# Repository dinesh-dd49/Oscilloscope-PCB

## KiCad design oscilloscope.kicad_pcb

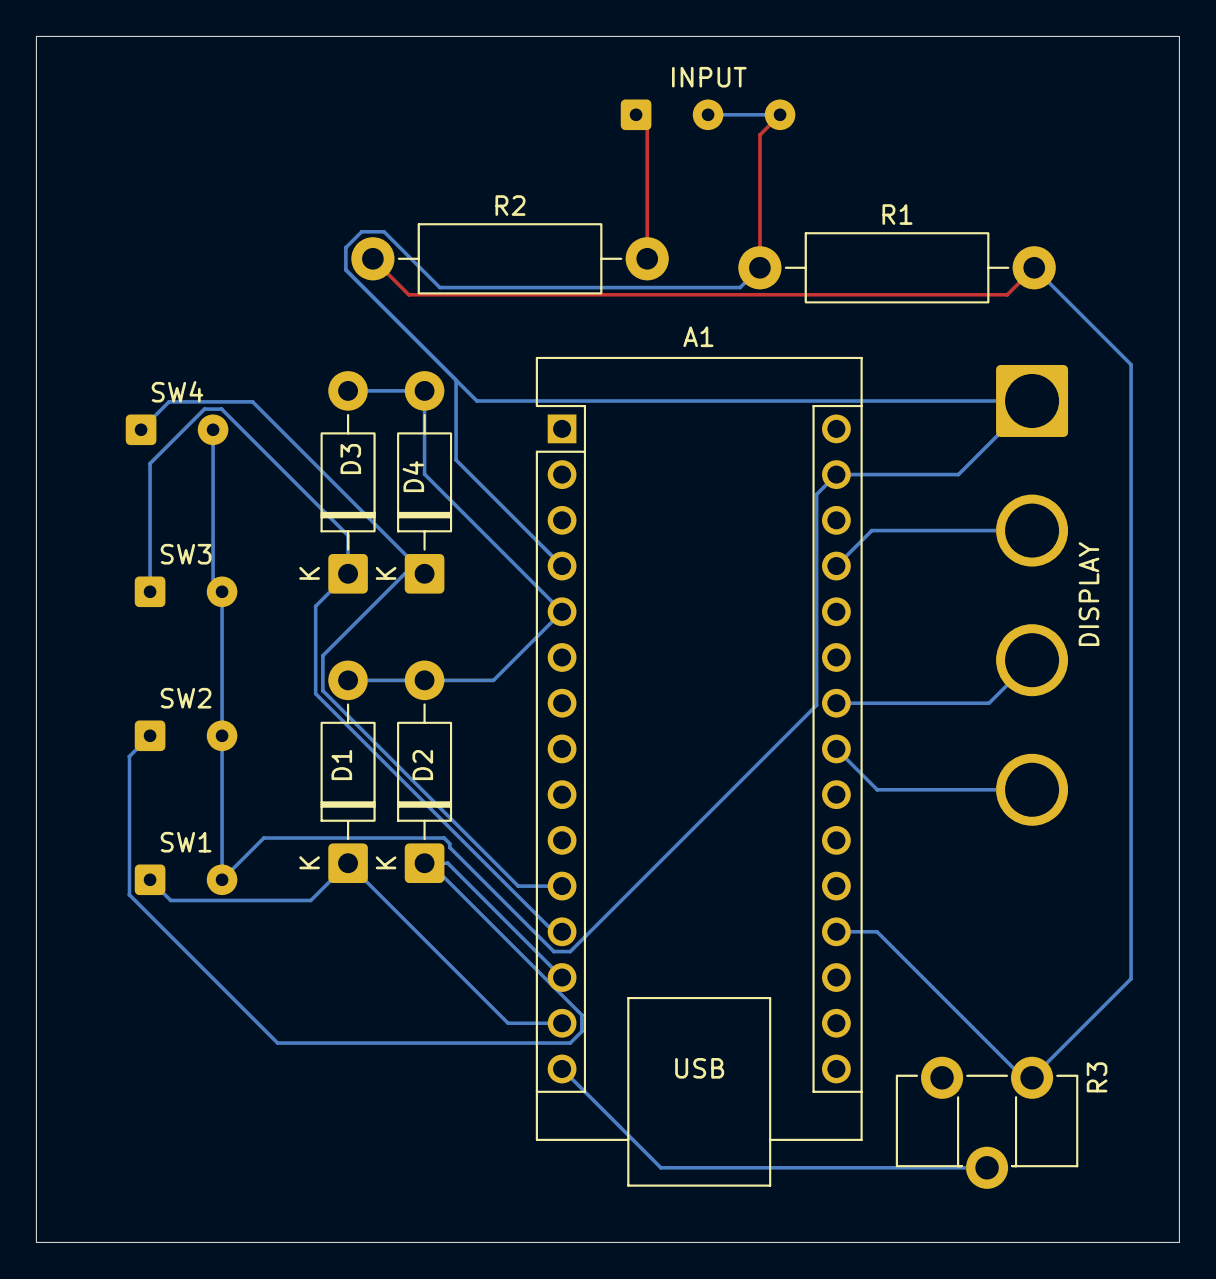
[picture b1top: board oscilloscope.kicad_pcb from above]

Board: 2 copper layers, 63.5 x 67.0 mm, 14 parts (0 on the bottom side), 12 nets.

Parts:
A1: Arduino_Nano_v3.x; Arduino_Nano
D1, D2, D3, D4: 1N4007; D_DO-41_SOD81_P10.16mm_Horizontal
DISPLAY: ER_OLEDM0.91_1x-I2C; SolderWire-2.5sqmm_1x04_P7.2mm_D2.4mm_OD3.6mm
INPUT: Barrel_Jack_Switch_Pin3Ring; SolderWire-0.15sqmm_1x03_P4mm_D0.5mm_OD1.5mm
R1: 100k; R_Axial_DIN0411_L9.9mm_D3.6mm_P15.24mm_Horizontal
R2: 390K; R_Axial_DIN0411_L9.9mm_D3.6mm_P15.24mm_Horizontal
R3: 10K; Potentiometer_ACP_CA9-H5_Horizontal
SW1, SW2, SW3, SW4: SW_Push; SolderWire-0.15sqmm_1x02_P4mm_D0.5mm_OD1.5mm

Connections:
/K1: A1.14 (D11), D1.1 (K), SW1.1
/K2: A1.13 (D10), D2.1 (K), SW2.1
/K3: A1.12 (D9), D3.1 (K), SW3.1
/K4: A1.11 (D8), D4.1 (K), SW4.1
/di: A1.5 (D2), D1.2 (A), D2.2 (A), D3.2 (A), D4.2 (A)
/dis_vol: A1.27 (+5V), DISPLAY.2 (VCC)
/scl: A1.24 (A5), DISPLAY.3 (SCL)
/sda: A1.23 (A4), DISPLAY.4 (SDA)
/sig: A1.19 (A0), R1.2, R2.1, R3.1
/sig_in: INPUT.1, R2.2
GND: A1.4 (GND), A1.29 (GND), DISPLAY.1 (GND), INPUT.2, INPUT.3, R1.1, SW1.2, SW2.2, SW3.2, SW4.2
unnamed: A1.15 (D12), R3.2
